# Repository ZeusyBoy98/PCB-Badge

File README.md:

# PCB-Badge
Intro project for Fallout, cool badge in the shape of lightning bolt (Because ZeusyBoy). Has NFC so people can get my github.

## BOM
| Item                            | Quantity |
| ------------------------------- | -------- |
| NT3H2111W0FT1X (NFC Controller) | 1        |
| Yellow LED 0805                 | 1        |
| Capacitor 220nf 0805            | 1        |
| Resistor 47Ω 0603               | 1        |

## Images

## Slack
@ZeusyBoy

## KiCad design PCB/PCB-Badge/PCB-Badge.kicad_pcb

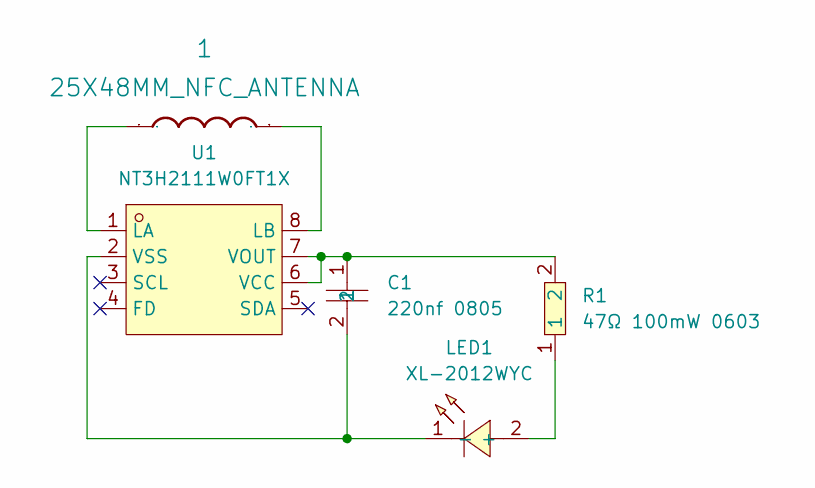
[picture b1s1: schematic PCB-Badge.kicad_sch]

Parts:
1: 25X48MM_NFC_ANTENNA
C1: 220nf 0805; C0805; LCSC Part C5153
LED1: XL-2012WYC; LED0805-RD_YELLOW; LCSC Part C7371914
R1: 47Ω 100mW 0603; 47_100mW_0603; LCSC Part C140088
U1: NT3H2111W0FT1X; NFC_TH; LCSC Part C2654859

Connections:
unnamed: LED1.2 (+), R1.1
unnamed: C1.2, LED1.1 (-), U1.2 (VSS)
unnamed: 1.P$2, U1.1 (LA)
unnamed: 1.P$1, U1.8 (LB)
unnamed: C1.1, R1.2, U1.6 (VCC), U1.7 (VOUT)

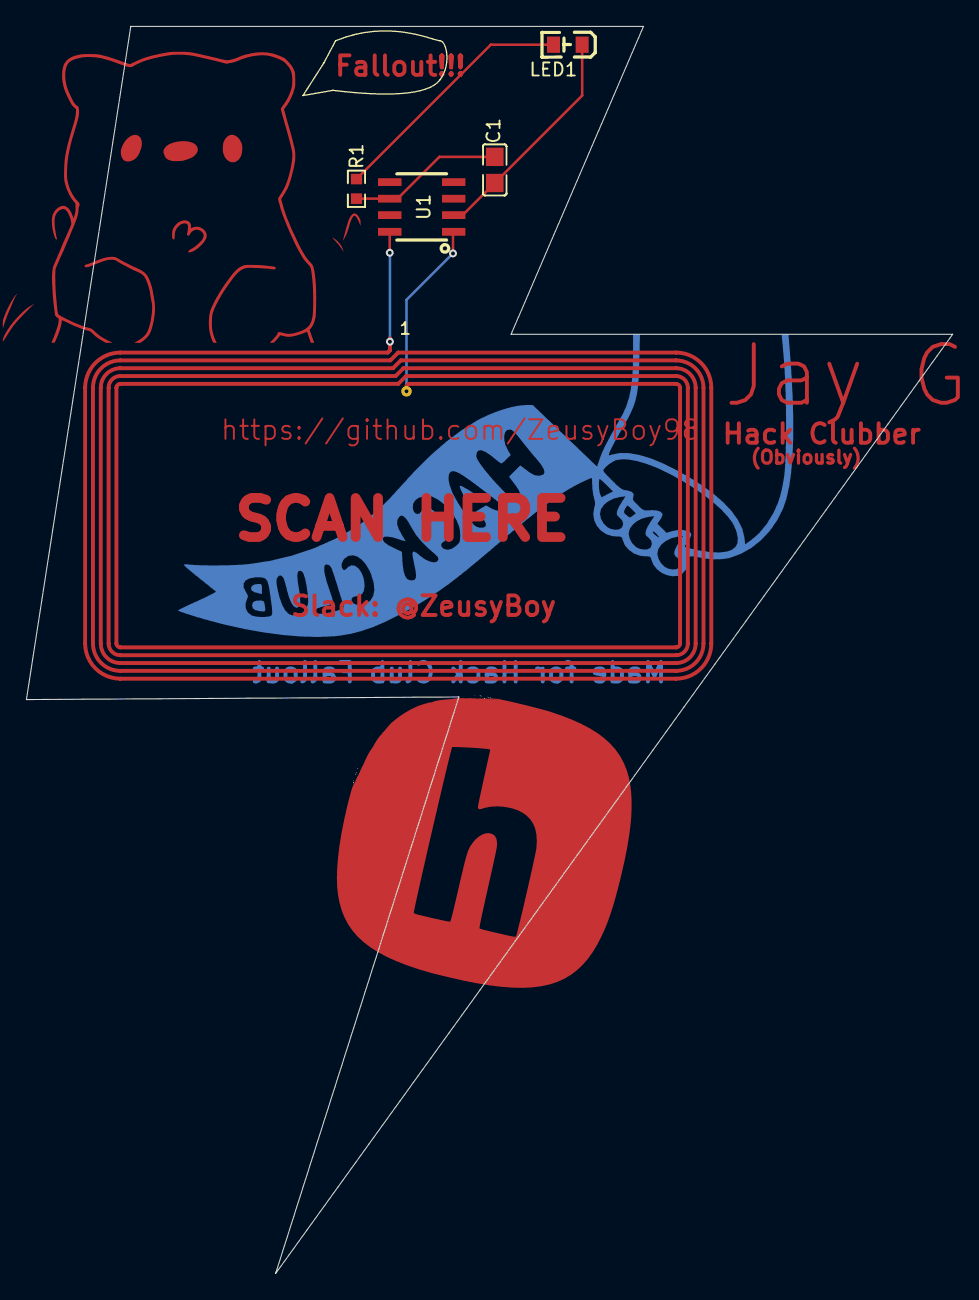
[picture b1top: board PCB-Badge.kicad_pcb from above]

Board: 2 copper layers, 71.0 x 95.6 mm, 5 parts (0 on the bottom side), 5 nets.
